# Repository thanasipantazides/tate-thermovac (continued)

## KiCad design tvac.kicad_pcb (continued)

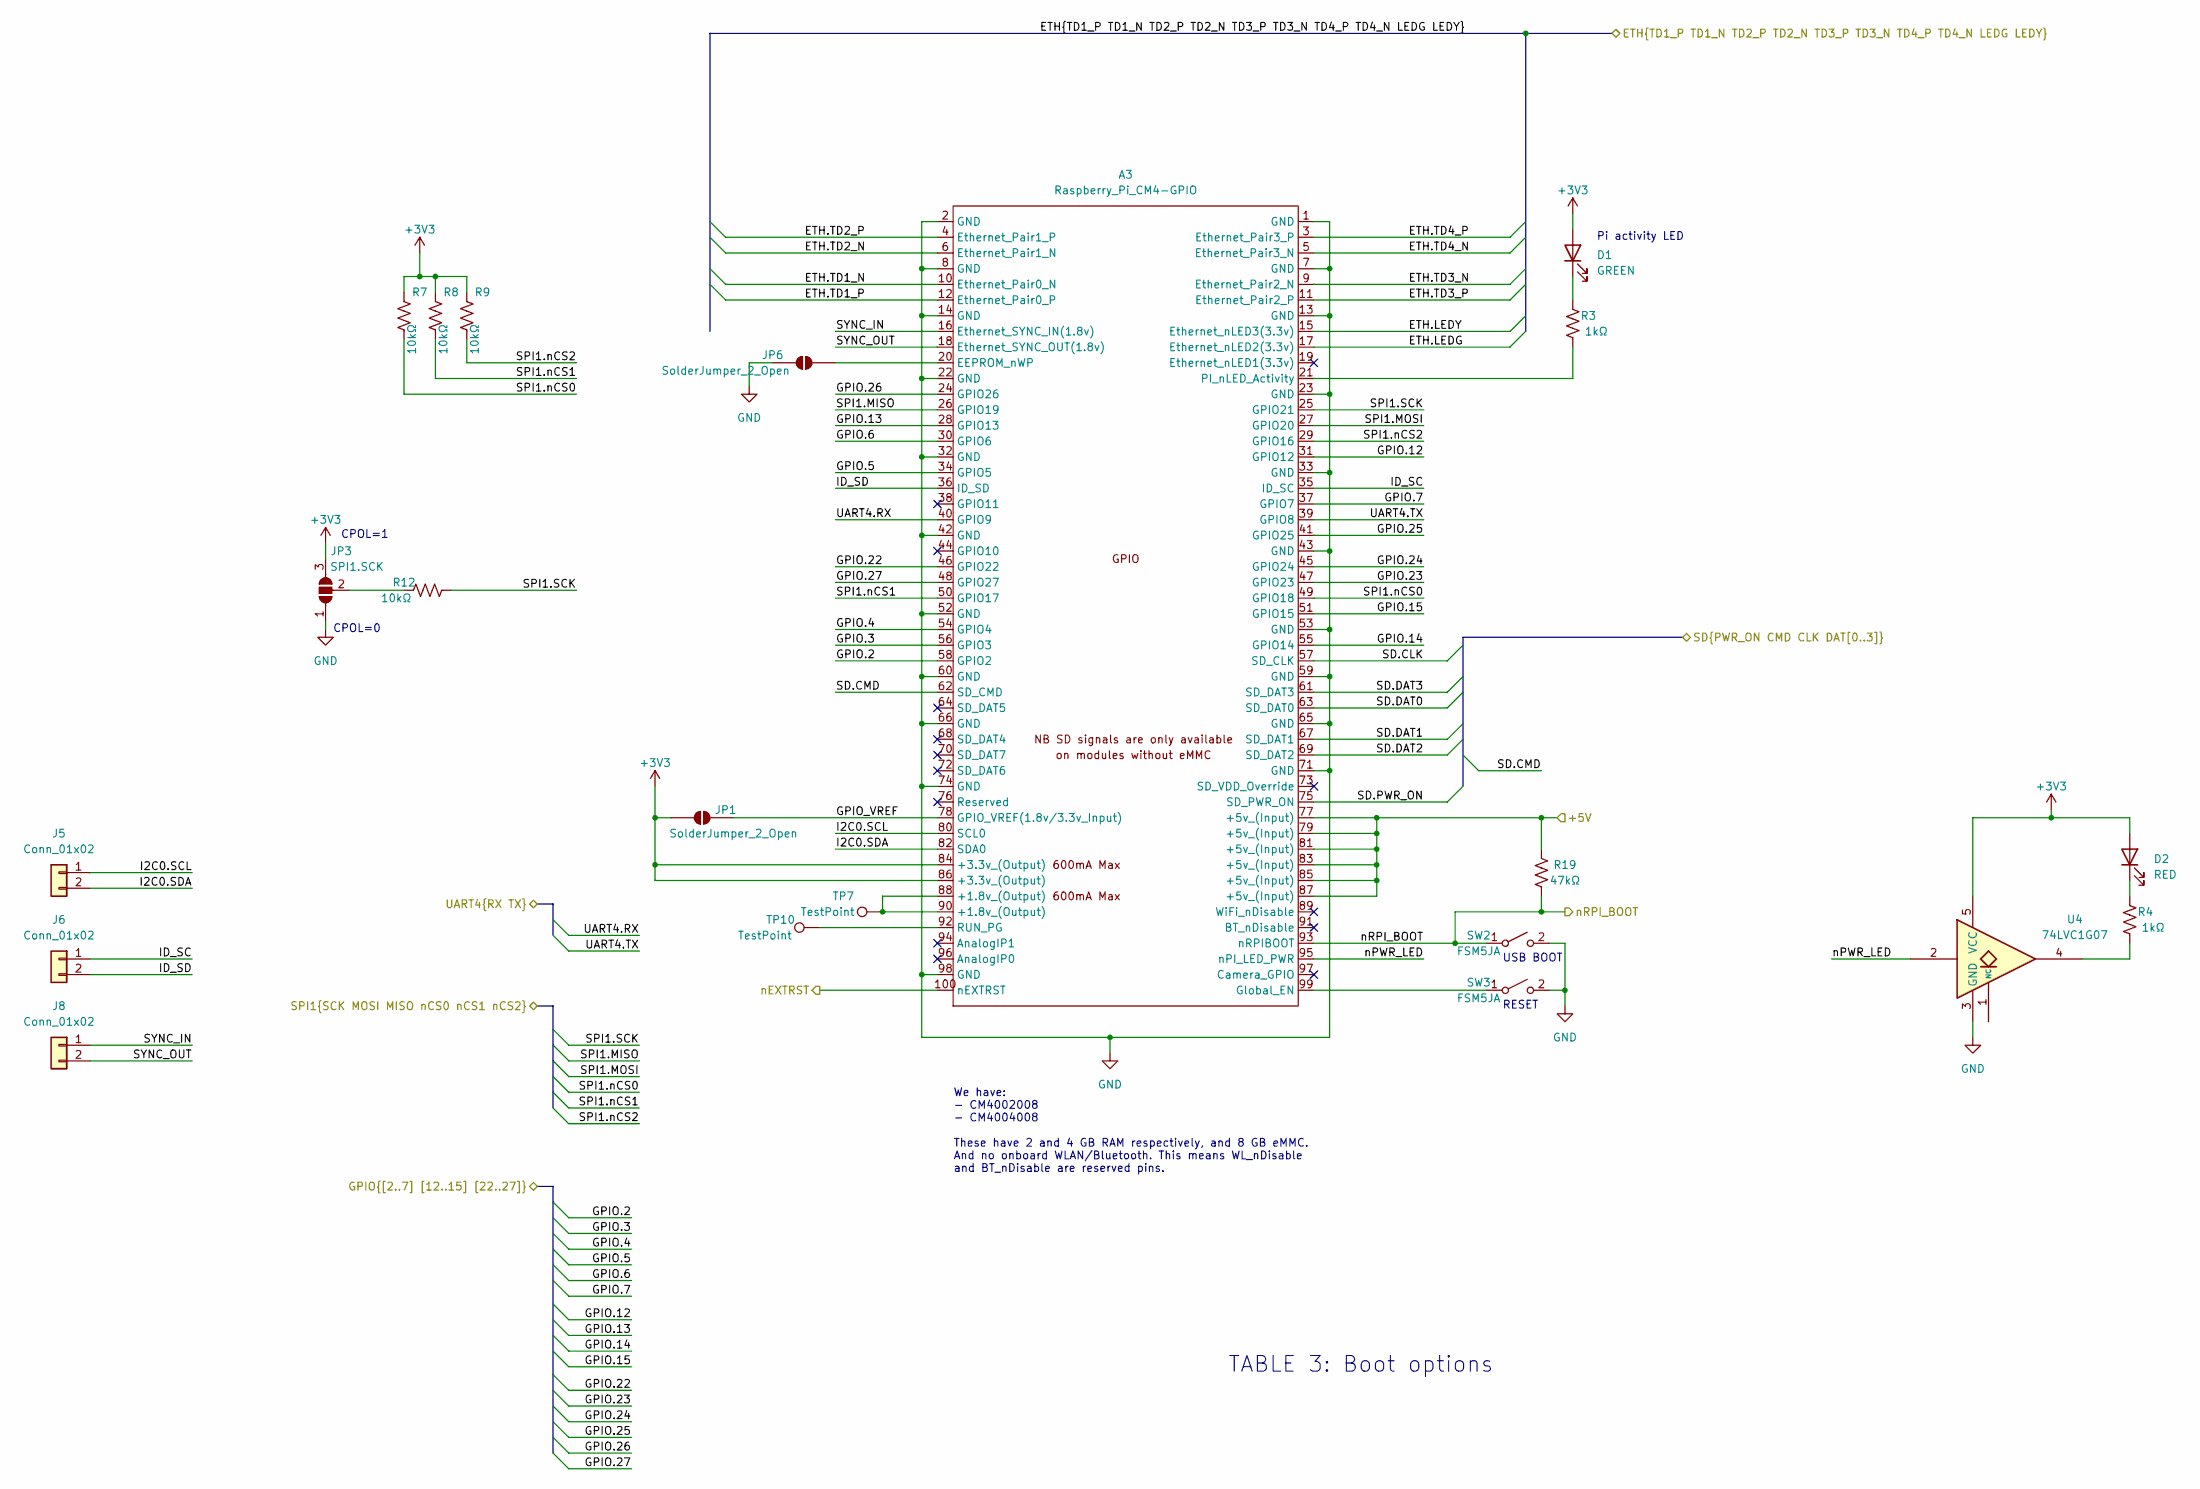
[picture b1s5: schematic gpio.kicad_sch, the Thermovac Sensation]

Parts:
A3: Raspberry_Pi_CM4-GPIO; Hirose_DF40HC(3.0)-100DS-0.4V_2x50_P0.4mm_RPi_CM4-GPIO
D1: GREEN; LED_1206_3216Metric; Digikey 160-1404-1-ND
D2: RED; LED_1206_3216Metric; Digikey 160-1405-1-ND
J5, J6, J8: Conn_01x02; PinHeader_1x02_P2.54mm_Vertical
JP1, JP6: SolderJumper_2_Open; SolderJumper-2_P1.3mm_Open_RoundedPad1.0x1.5mm
JP3: SPI1.SCK; SolderJumper-3_P1.3mm_Open_RoundedPad1.0x1.5mm
R3, R4: 1kΩ; R_0603_1608Metric
R7, R8, R9, R12: 10kΩ; R_0603_1608Metric
R19: 47kΩ; R_0603_1608Metric
SW2: FSM5JA; SW_DIP_SPSTx01_Slide_9.78x4.72mm_W7.62mm_P2.54mm
SW3: FSM5JA; SW_PUSH_6mm
TP7, TP10: TestPoint; TestPoint_Pad_D2.5mm
U4: 74LVC1G07; SOT-23-5

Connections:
+3V3: A3.84 (+3.3v_(Output)), A3.86 (+3.3v_(Output)), D1.2 (A), D2.2 (A), JP1.1 (A), JP3.3 (B), R7.2, R8.2, R9.2, U4.5 (VCC); also elsewhere on the board
/+5V: A3.77 (+5v_(Input)), A3.79 (+5v_(Input)), A3.81 (+5v_(Input)), A3.83 (+5v_(Input)), A3.85 (+5v_(Input)), A3.87 (+5v_(Input)), R19.2; also elsewhere on the board
/adc/SPI1.MISO: A3.26 (GPIO19); also elsewhere on the board
/adc/SPI1.MOSI: A3.27 (GPIO20); also elsewhere on the board
/adc/SPI1.SCK: A3.25 (GPIO21), R12.1; also elsewhere on the board
/adc/SPI1.nCS0: A3.49 (GPIO18), R7.1; also elsewhere on the board
/adc/SPI1.nCS1: A3.50 (GPIO17), R8.1; also elsewhere on the board
/adc/SPI1.nCS2: A3.29 (GPIO16), R9.1; also elsewhere on the board
/gpio/ETH.LEDG: A3.17 (Ethernet_nLED2(3.3v)); also elsewhere on the board
/gpio/ETH.LEDY: A3.15 (Ethernet_nLED3(3.3v)); also elsewhere on the board
/gpio/ETH.TD1_N: A3.10 (Ethernet_Pair0_N); also elsewhere on the board
/gpio/ETH.TD1_P: A3.12 (Ethernet_Pair0_P); also elsewhere on the board
/gpio/ETH.TD2_N: A3.6 (Ethernet_Pair1_N); also elsewhere on the board
/gpio/ETH.TD2_P: A3.4 (Ethernet_Pair1_P); also elsewhere on the board
/gpio/ETH.TD3_N: A3.9 (Ethernet_Pair2_N); also elsewhere on the board
/gpio/ETH.TD3_P: A3.11 (Ethernet_Pair2_P); also elsewhere on the board
/gpio/ETH.TD4_N: A3.5 (Ethernet_Pair3_N); also elsewhere on the board
/gpio/ETH.TD4_P: A3.3 (Ethernet_Pair3_P); also elsewhere on the board
/gpio/GPIO.2: A3.58 (GPIO2); also elsewhere on the board
/gpio/GPIO.3: A3.56 (GPIO3); also elsewhere on the board
/gpio/GPIO.4: A3.54 (GPIO4); also elsewhere on the board
/gpio/GPIO.5: A3.34 (GPIO5); also elsewhere on the board
/gpio/GPIO.6: A3.30 (GPIO6); also elsewhere on the board
/gpio/GPIO.7: A3.37 (GPIO7); also elsewhere on the board
/gpio/GPIO.12: A3.31 (GPIO12); also elsewhere on the board
/gpio/GPIO.13: A3.28 (GPIO13); also elsewhere on the board
/gpio/GPIO.14: A3.55 (GPIO14); also elsewhere on the board
/gpio/GPIO.15: A3.51 (GPIO15); also elsewhere on the board
/gpio/GPIO.22: A3.46 (GPIO22); also elsewhere on the board
/gpio/GPIO.23: A3.47 (GPIO23); also elsewhere on the board
/gpio/GPIO.24: A3.45 (GPIO24); also elsewhere on the board
/gpio/GPIO.25: A3.41 (GPIO25); also elsewhere on the board
/gpio/GPIO.26: A3.24 (GPIO26); also elsewhere on the board
/gpio/GPIO.27: A3.48 (GPIO27); also elsewhere on the board
/gpio/GPIO_VREF: A3.78 (GPIO_VREF(1.8v/3.3v_Input)), JP1.2 (B)
/gpio/I2C0.SCL: A3.80 (SCL0), J5.1
/gpio/I2C0.SDA: A3.82 (SDA0), J5.2
/gpio/ID_SC: A3.35 (ID_SC), J6.1
/gpio/ID_SD: A3.36 (ID_SD), J6.2
/gpio/SD.CLK: A3.57 (SD_CLK); also elsewhere on the board
/gpio/SD.CMD: A3.62 (SD_CMD); also elsewhere on the board
/gpio/SD.DAT0: A3.63 (SD_DAT0); also elsewhere on the board
/gpio/SD.DAT1: A3.67 (SD_DAT1); also elsewhere on the board
/gpio/SD.DAT2: A3.69 (SD_DAT2); also elsewhere on the board
/gpio/SD.DAT3: A3.61 (SD_DAT3); also elsewhere on the board
/gpio/SD.PWR_ON: A3.75 (SD_PWR_ON)
/gpio/SYNC_IN: A3.16 (Ethernet_SYNC_IN(1.8v)), J8.1
/gpio/SYNC_OUT: A3.18 (Ethernet_SYNC_OUT(1.8v)), J8.2
/gpio/UART4.RX: A3.40 (GPIO9); also elsewhere on the board
/gpio/UART4.TX: A3.39 (GPIO8); also elsewhere on the board
/gpio/nEXTRST: A3.100 (nEXTRST); also elsewhere on the board
/gpio/nPWR_LED: A3.95 (nPI_LED_PWR), U4.2
/gpio/nRPI_BOOT: A3.93 (nRPIBOOT), R19.1, SW2.1 (A); also elsewhere on the board
GND: A3.1 (GND), A3.2 (GND), A3.7 (GND), A3.8 (GND), A3.13 (GND), A3.14 (GND), A3.22 (GND), A3.23 (GND), A3.32 (GND), A3.33 (GND), A3.42 (GND), A3.43 (GND), A3.52 (GND), A3.53 (GND), A3.59 (GND), A3.60 (GND), A3.65 (GND), A3.66 (GND), A3.71 (GND), A3.74 (GND), A3.98 (GND), JP3.1 (A), JP6.1 (A), SW2.2 (B), SW3.2 (B), U4.3 (GND); also elsewhere on the board
unnamed: A3.88 (+1.8v_(Output)), A3.90 (+1.8v_(Output)), TP7.1 (1_1)
unnamed: A3.20 (EEPROM_nWP), JP6.2 (B)
unnamed: A3.99 (Global_EN), SW3.1 (A)
unnamed: A3.21 (PI_nLED_Activity), R3.1
unnamed: A3.92 (RUN_PG), TP10.1 (1_1)
unnamed: D1.1 (K), R3.2
unnamed: D2.1 (K), R4.2
unnamed: JP3.2 (C), R12.2
unnamed: R4.1, U4.4

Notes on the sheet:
TABLE 3: Boot options
CPOL=1
RESET
USB BOOT
We have: - CM4002008 - CM4004008 These have 2 and 4 GB RAM respectively, and 8 GB eMMC. And no onboard WLAN/Bluetooth. This means WL_nDisable and BT_nDisable are reserved pins.
Pi activity LED
CPOL=0

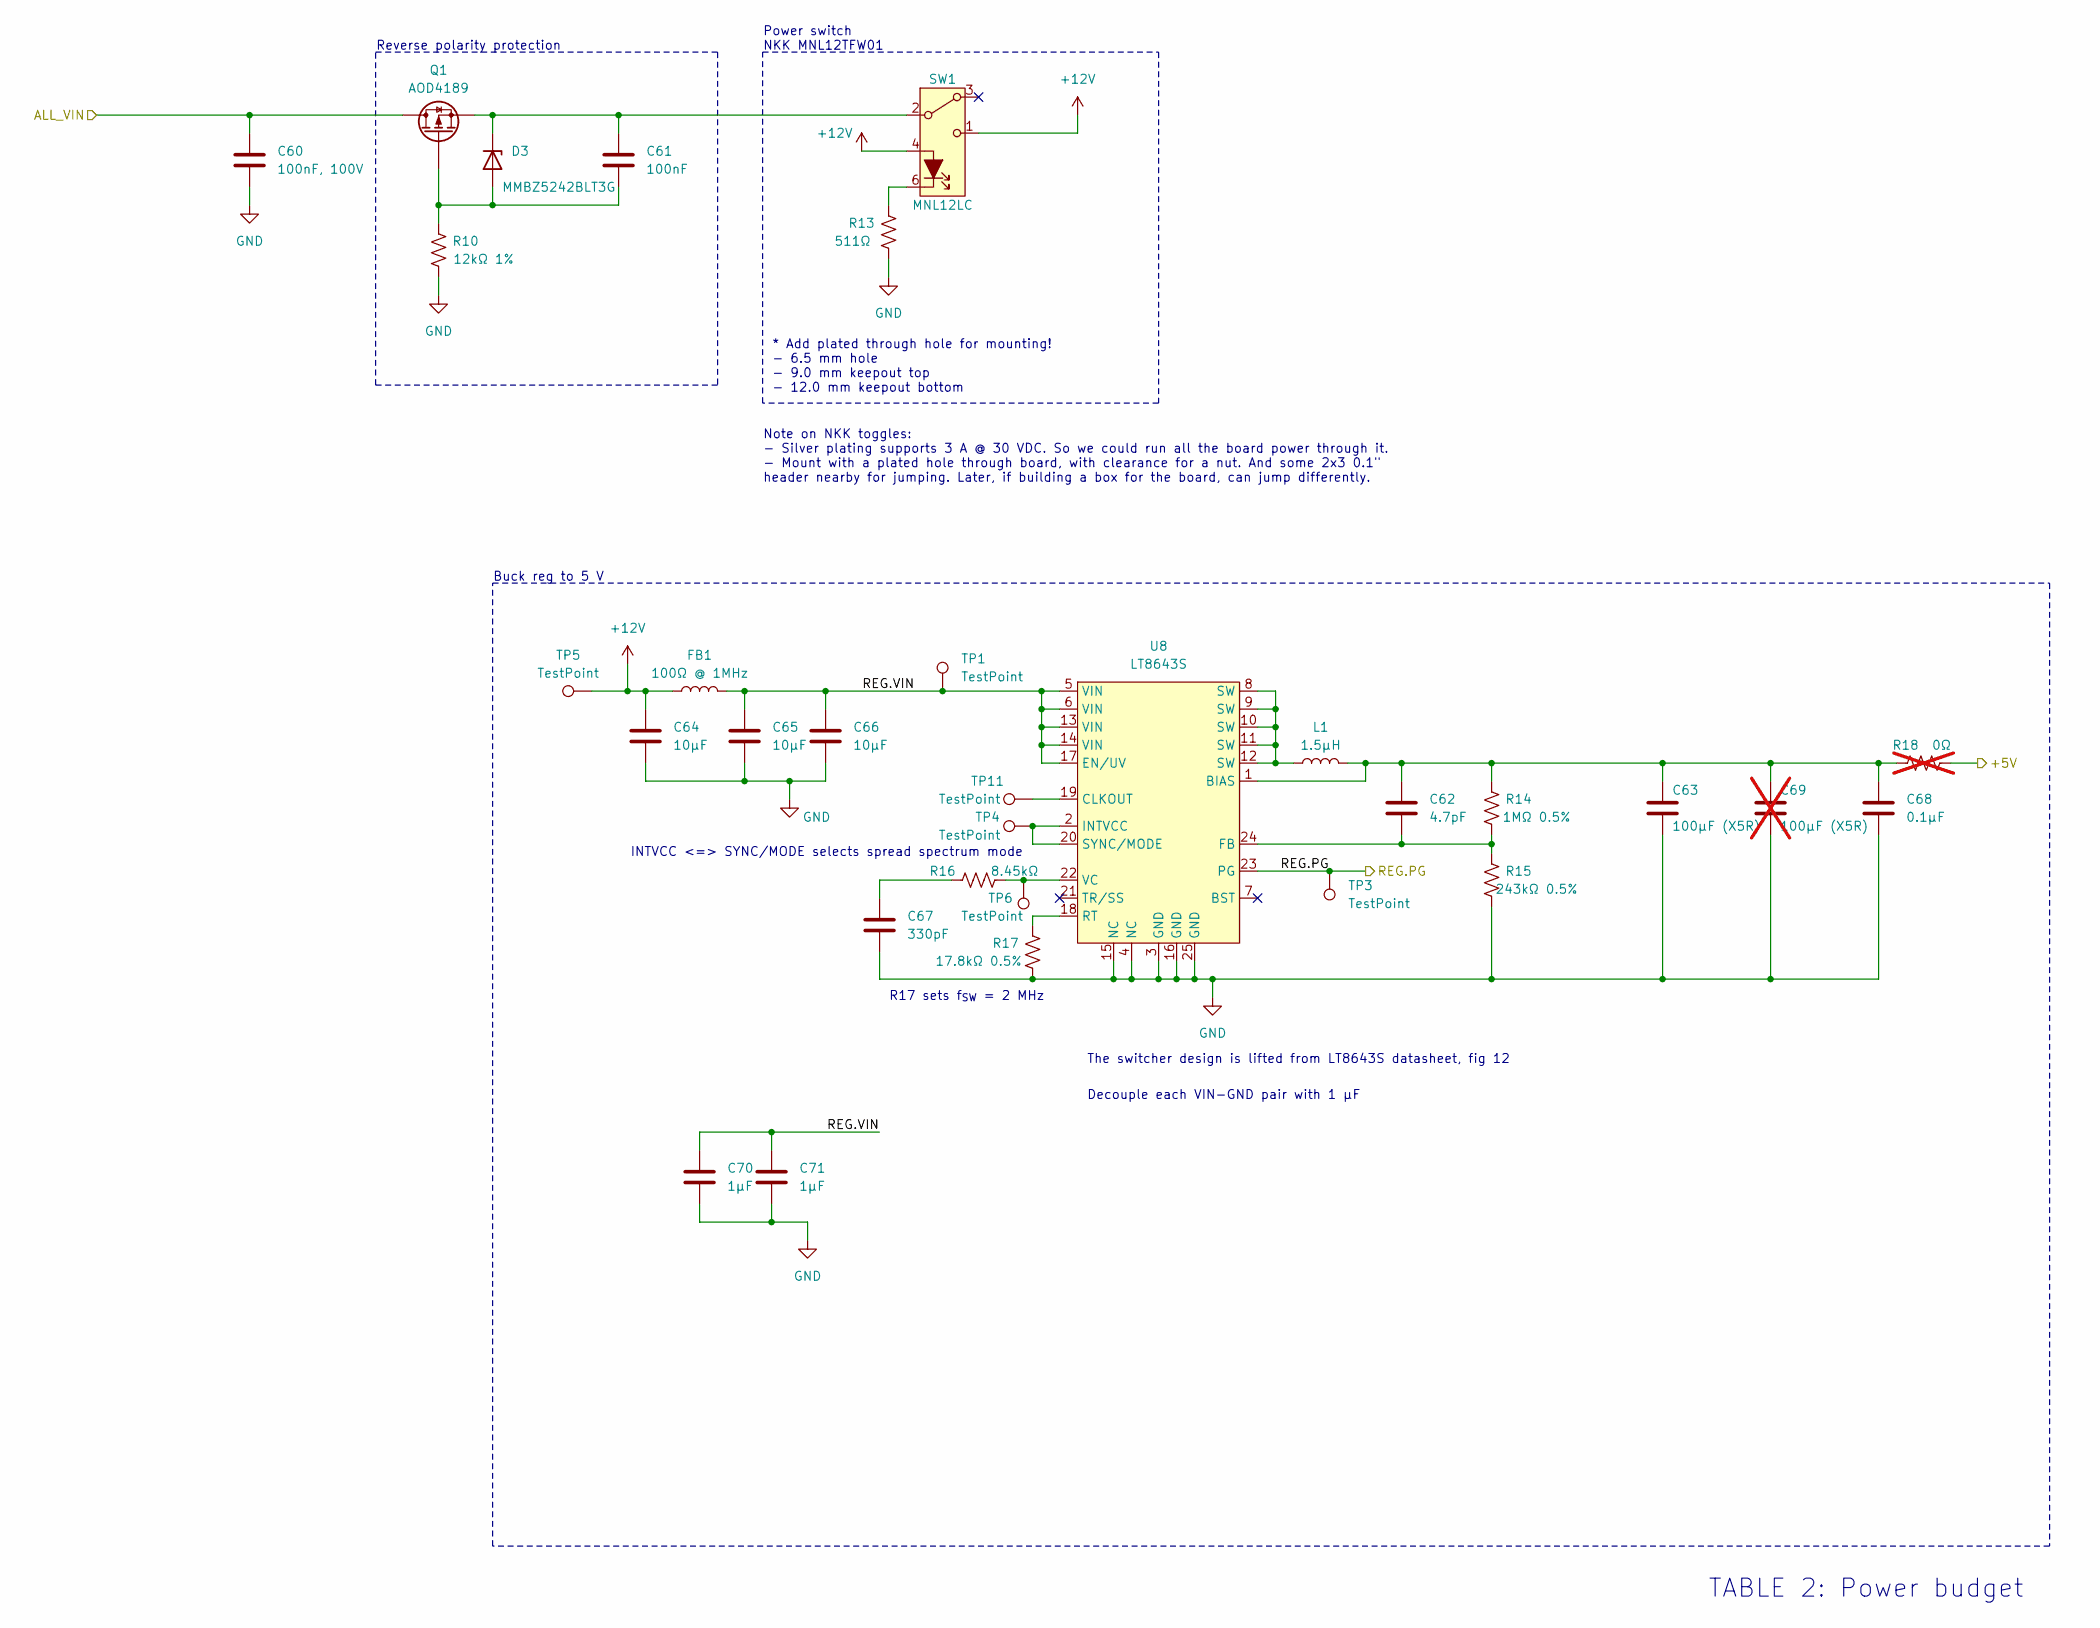
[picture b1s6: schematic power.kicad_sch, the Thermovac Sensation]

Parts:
C60: 100nF, 100V; C_1210_3225Metric
C61: 100nF; C_0603_1608Metric
C62: 4.7pF; C_0603_1608Metric
C63: 100µF (X5R); C_1210_3225Metric
C64, C65, C66: 10µF; C_1210_3225Metric
C67: 330pF; C_0603_1608Metric
C68: 0.1µF; C_0603_1608Metric
C69: 100µF (X5R); C_1210_3225Metric; not fitted
C70, C71: 1µF; C_0603_1608Metric
D3: MMBZ5242BLT3G; SOT-23; Digikey MMBZ5242BLT3GOSCT-ND
FB1: 100Ω @ 1MHz; C_1812_4532Metric; Digikey 732-3431-1-ND
L1: 1.5µH; L_Wuerth_HCI-1365
Q1: AOD4189; TO-252-2; Digikey 785-1351-1-ND
R10: 12kΩ 1%; R_0603_1608Metric
R13: 511Ω; R_0603_1608Metric
R14: 1MΩ 0.5%; R_0603_1608Metric
R15: 243kΩ 0.5%; R_0603_1608Metric
R16: 8.45kΩ; R_0603_1608Metric
R17: 17.8kΩ 0.5%; R_0603_1608Metric
R18: 0Ω; R_1210_3225Metric; not fitted
SW1: MNL12LC; PinSocket_2x03_P2.54mm_Vertical
TP1, TP3, TP4, TP5, TP6, TP11: TestPoint; TestPoint_Pad_D2.5mm
U8: LT8643S; QFN-24-1EP_4x4mm_P0.5mm_EP2.75x2.75mm

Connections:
+12V: C64.1, FB1.1, SW1.1 (C), SW1.4 (KR), TP5.1 (1_1)
/+5V: R18.2; also elsewhere on the board
/power/ALL_VIN: C60.1, Q1.D; also elsewhere on the board
/power/REG.PG: TP3.1 (1_1), U8.23 (PG)
/power/REG.VIN: C65.1, C66.1, C70.1, C71.1, FB1.2, TP1.1 (1_1), U8.5 (VIN), U8.6 (VIN), U8.13 (VIN), U8.14 (VIN), U8.17 (EN/UV)
GND: C60.2, C63.2, C64.2, C65.2, C66.2, C67.2, C68.2, C69.2, C70.2, C71.2, R10.1, R13.1, R15.1, R17.2, U8.3 (GND), U8.4 (NC), U8.15 (NC), U8.16 (GND), U8.25 (GND); also elsewhere on the board
unnamed: C67.1, R16.2
unnamed: C61.2, D3.1 (A), Q1.G, R10.2
unnamed: C61.1, D3.3 (K), Q1.S, SW1.2 (B)
unnamed: L1.1, U8.8 (SW), U8.9 (SW), U8.10 (SW), U8.11 (SW), U8.12 (SW)
unnamed: R13.2, SW1.6 (KG)
unnamed: C62.1, C63.1, C68.1, C69.1, L1.2, R14.2, R18.1, U8.1 (BIAS)
unnamed: TP11.1 (1_1), U8.19 (CLKOUT)
unnamed: C62.2, R14.1, R15.2, U8.24 (FB)
unnamed: TP4.1 (1_1), U8.2 (INTVCC), U8.20 (SYNC/MODE)
unnamed: R17.1, U8.18 (RT)
unnamed: R16.1, TP6.1 (1_1), U8.22 (VC)

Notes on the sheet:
TABLE 2: Power budget
INTVCC <=> SYNC/MODE selects spread spectrum mode
Power switch NKK MNL12TFW01
Note on NKK toggles: - Silver plating supports 3 A @ 30 VDC. So we could run all the board power through it. - Mount with a plated hole through board, with clearance for a nut. And some 2x3 0.1" header nearby for jumping. Later, if building a box for the board, can jump differently.
Buck reg to 5 V
R17 sets f_{SW} = 2 MHz
Decouple each VIN-GND pair with 1 µF
The switcher design is lifted from LT8643S datasheet, fig 12
* Add plated through hole for mounting! - 6.5 mm hole - 9.0 mm keepout top - 12.0 mm keepout bottom
Reverse polarity protection

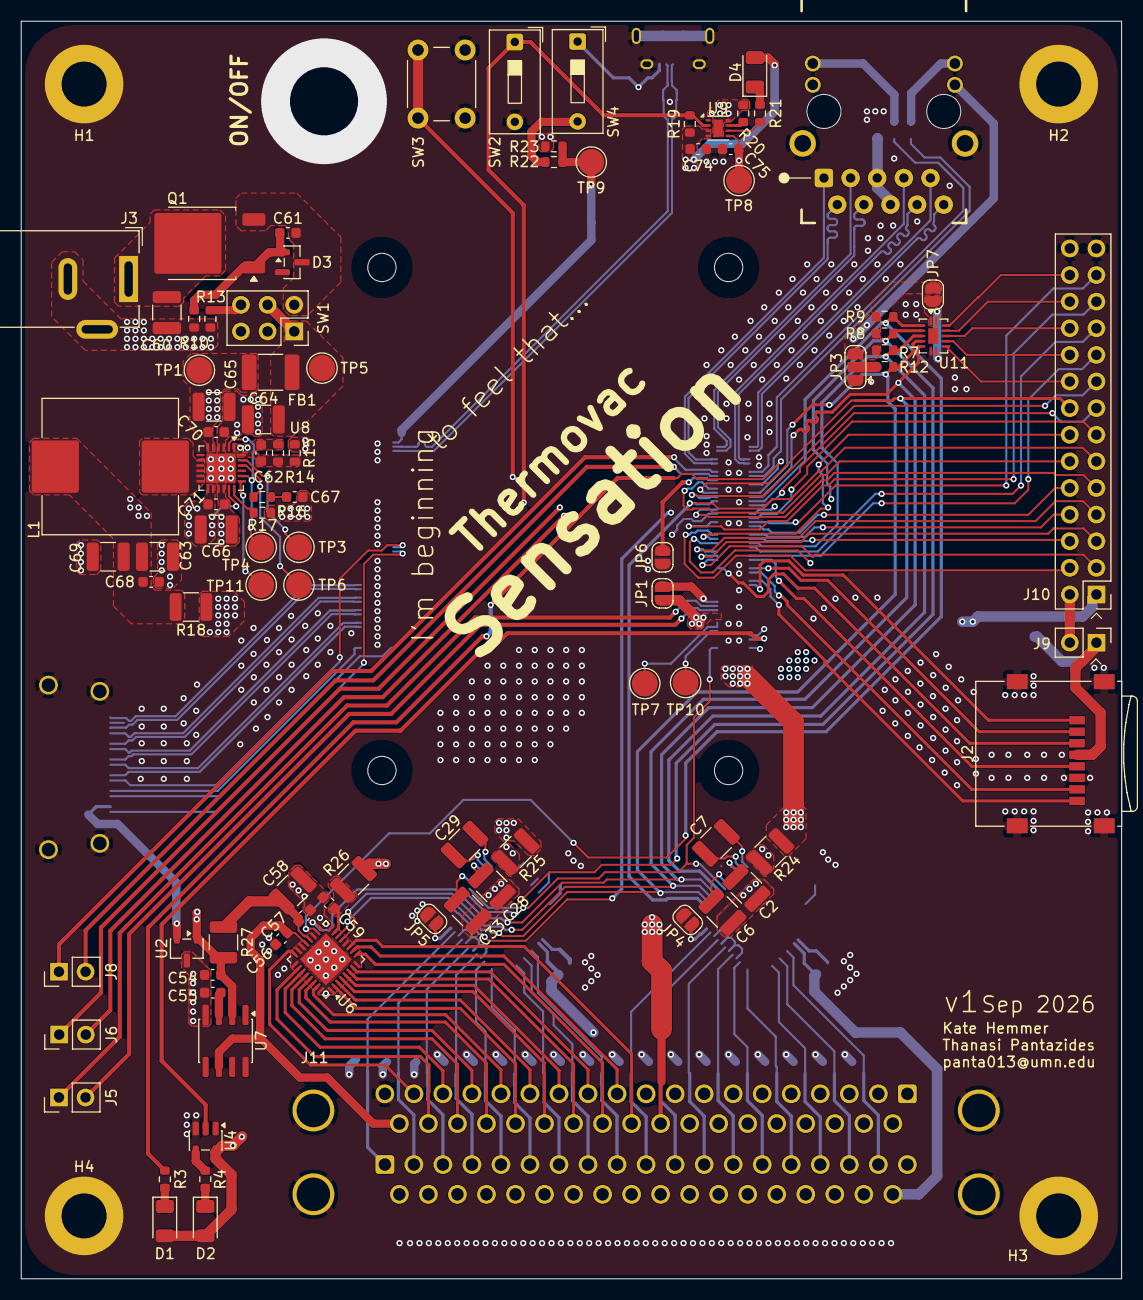
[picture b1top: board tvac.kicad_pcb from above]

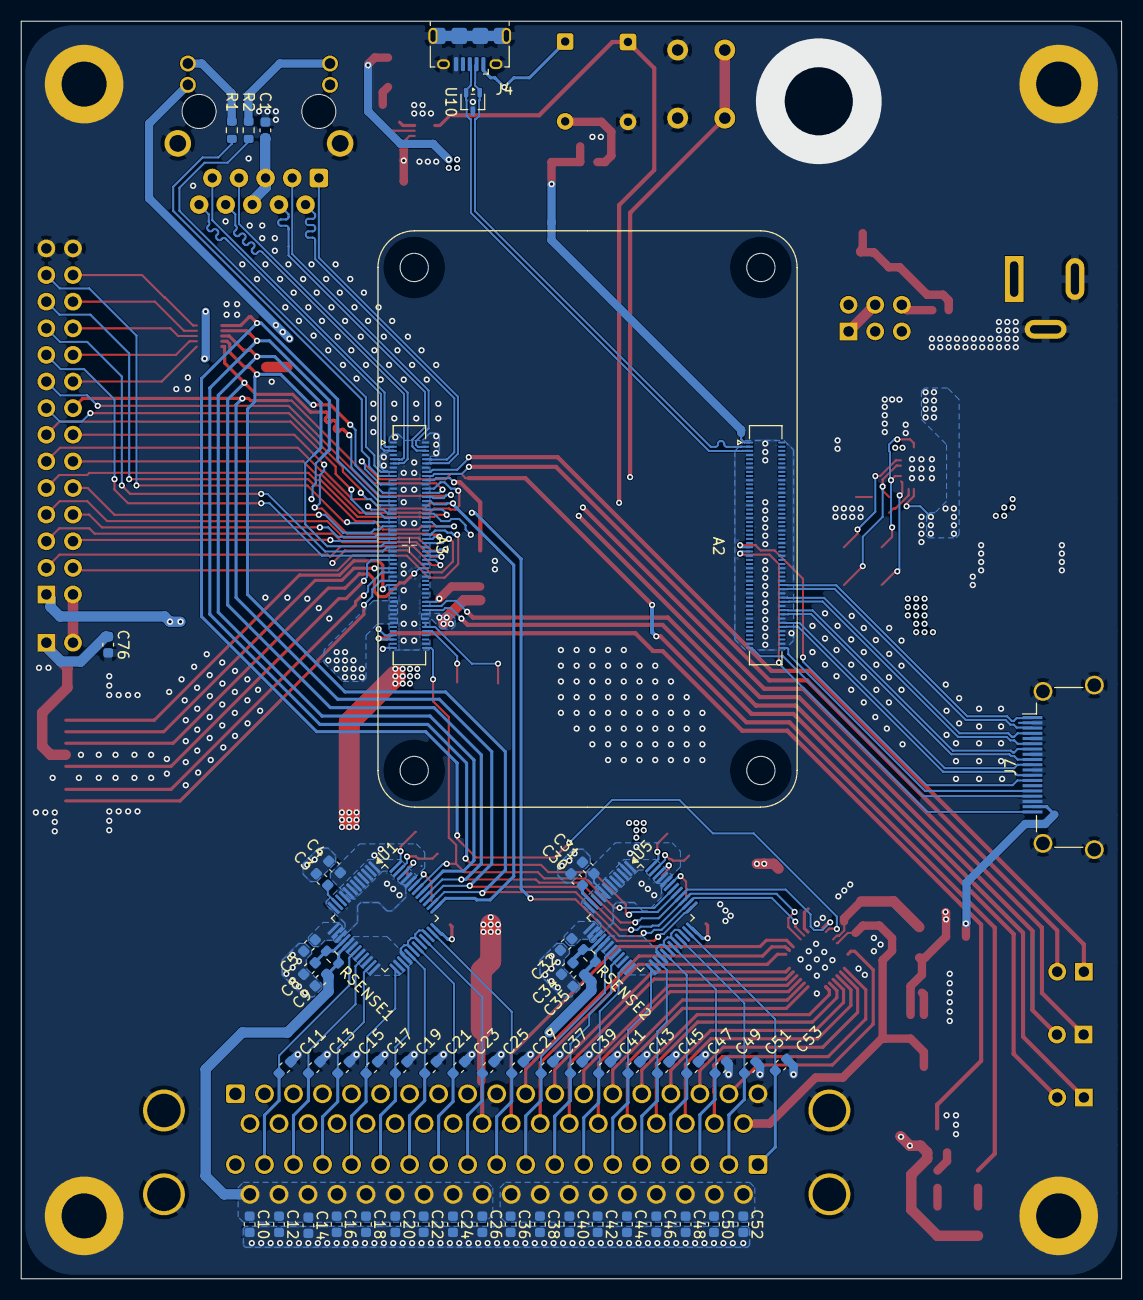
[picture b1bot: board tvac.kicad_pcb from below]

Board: 4 copper layers, 105.0 x 120.0 mm, 154 parts (59 on the bottom side), 166 nets.
